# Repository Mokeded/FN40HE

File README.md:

# FN40HE

FN40HE is a 40%, Hall-effect mechanical keyboard PCB and firmware project. It
adapts the FN40 layout to magnetic (Hall-effect) switches, giving every key
analog actuation — per-key adjustable actuation points, Rapid Trigger,
SOCD/Null Bind, Dynamic Keystroke, and analog gamepad output — instead of a
fixed mechanical trip point.

## What's in this repository

- **KiCad hardware design** — `FN40HE.kicad_pro`/`.kicad_sch`/`.kicad_pcb`,
  a two-layer PCB with 57 independent Hall-sensor channels multiplexed down
  to an 8-channel ADC scan order, plus `FN40HE-plate.step` for the
  mechanical plate reference. `FN40_Project.pretty`, `lib`, `fp-lib-table`,
  and `sym-lib-table` are the local footprint/symbol libraries needed to
  open the project without external dependencies.
- **Firmware** (`firmware/`) — a [libhmk](https://github.com/libhmk/libhmk)-derived
  build configured for the `fn40he` board target, with prebuilt DFU
  artifacts in `firmware/build/` and full source under `firmware/source/`
  for rebuilding.
- **Manufacturing and assembly data** — `FN40HE-BOM.csv` (bill of
  materials for all assembly variants), `FN40HE-ASSEMBLY.md` (which
  mutually-exclusive switch/sensor positions to populate per variant),
  `FN40HE-sensor-map.csv` and `FN40HE-mux-map.csv` (physical-to-firmware
  key mapping), and `manufacturing/FN40HE-Gerbers-JLCPCB.zip` (bare-board
  fab archive).
- **Verification records** — `FN40HE-DRC.rpt` and `FN40HE-ERC.rpt` (PCB/
  schematic check reports) and `FN40HE-J1-WAIVER.md` (documented DRC
  waiver and inspection requirement for the J1 connector footprint).

See `FN40HE-README.md` for release status, build/flash instructions, and
firmware feature details.

## Assembly variants

The board supports three populate/DNP variants sharing one PCB:
**Universal57** (all 57 sensors populated — the released default),
**SplitSpace**, and **SevenUnit** (alternate bottom-row layouts). See
`FN40HE-ASSEMBLY.md` and the DNP columns in `FN40HE-BOM.csv` before
ordering assembly.

## License

This project incorporates GPLv3-derived hardware design and firmware work.
See `LICENSE`. Retain source, license, and attribution when redistributing
modifications.

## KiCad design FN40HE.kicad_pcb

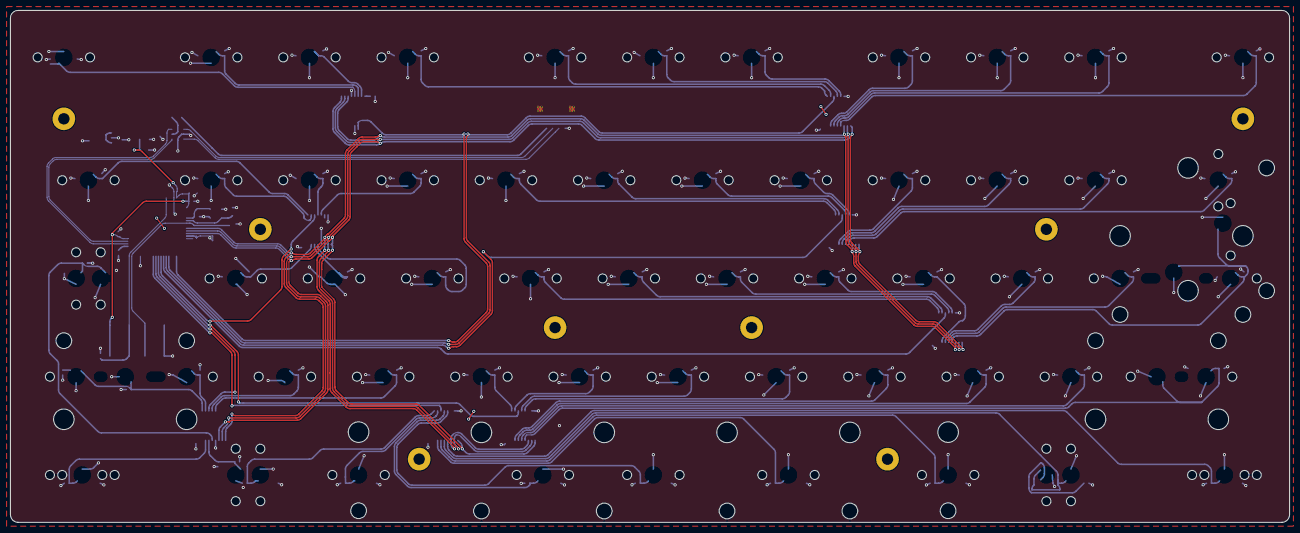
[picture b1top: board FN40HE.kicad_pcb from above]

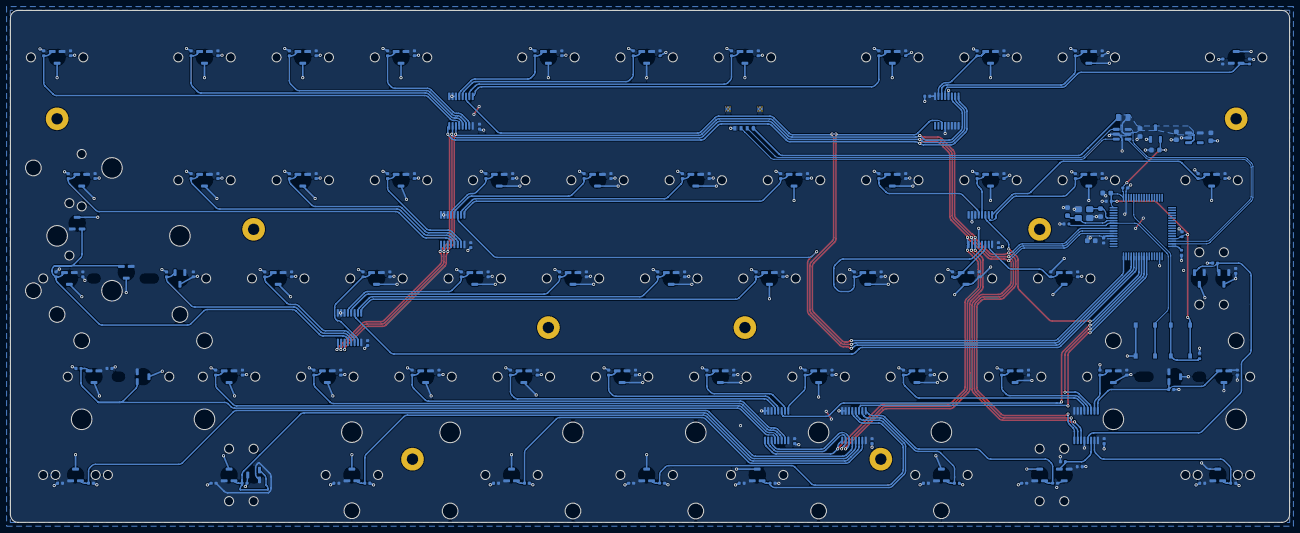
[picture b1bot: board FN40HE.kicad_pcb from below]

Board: 2 copper layers, 248.0 x 99.2 mm, 234 parts (219 on the bottom side), 82 nets.

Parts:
AM1: SN74LV4051A; AM1_TSSOP-16_4.4x5mm_P0.65mm
AM2: SN74LV4051A; AM2_TSSOP-16_4.4x5mm_P0.65mm
AM3: SN74LV4051A; AM3_TSSOP-16_4.4x5mm_P0.65mm
AM4: SN74LV4051A; AM4_TSSOP-16_4.4x5mm_P0.65mm
AM5: SN74LV4051A; AM5_TSSOP-16_4.4x5mm_P0.65mm
AM6: SN74LV4051A; AM6_TSSOP-16_4.4x5mm_P0.65mm
AM7: SN74LV4051A; AM7_TSSOP-16_4.4x5mm_P0.65mm
AM8: SN74LV4051A; AM8_TSSOP-16_4.4x5mm_P0.65mm
C1: 100n; C1_C_0402_1005Metric
C2: 4.7n; C2_C_0402_1005Metric
C3: 100n; C3_C_0402_1005Metric
C4: 4.7n; C4_C_0402_1005Metric
C5: 100n; C5_C_0402_1005Metric
C6: 4.7n; C6_C_0402_1005Metric
C7: 100n; C7_C_0402_1005Metric
C8: 4.7n; C8_C_0402_1005Metric
C9: 100n; C9_C_0402_1005Metric
C10: 4.7n; C10_C_0402_1005Metric
C11: 100n; C11_C_0402_1005Metric
C12: 4.7n; C12_C_0402_1005Metric
C13: 100n; C13_C_0402_1005Metric
C14: 4.7n; C14_C_0402_1005Metric
C15: 100n; C15_C_0402_1005Metric
C16: 4.7n; C16_C_0402_1005Metric
C17: 100n; C17_C_0402_1005Metric
C18: 4.7n; C18_C_0402_1005Metric
C19: 100n; C19_C_0402_1005Metric
C20: 4.7n; C20_C_0402_1005Metric
C21: 100n; C21_C_0402_1005Metric
C22: 4.7n; C22_C_0402_1005Metric
C23: 100n; C23_C_0402_1005Metric
C24: 4.7n; C24_C_0402_1005Metric
C25: 100n; C25_C_0402_1005Metric
C26: 4.7n; C26_C_0402_1005Metric
C27: 100n; C27_C_0402_1005Metric
C28: 4.7n; C28_C_0402_1005Metric
C29: 100n; C29_C_0402_1005Metric
C30: 4.7n; C30_C_0402_1005Metric
C31: 100n; C31_C_0402_1005Metric
C32: 4.7n; C32_C_0402_1005Metric
C33: 100n; C33_C_0402_1005Metric
C34: 4.7n; C34_C_0402_1005Metric
C35: 100n; C35_C_0402_1005Metric
C36: 4.7n; C36_C_0402_1005Metric
C37: 100n; C37_C_0402_1005Metric
C38: 4.7n; C38_C_0402_1005Metric
C39: 100n; C39_C_0402_1005Metric
C40: 4.7n; C40_C_0402_1005Metric
C41: 100n; C41_C_0402_1005Metric
C42: 4.7n; C42_C_0402_1005Metric
C43: 100n; C43_C_0402_1005Metric
C44: 4.7n; C44_C_0402_1005Metric
C45: 100n; C45_C_0402_1005Metric
C46: 4.7n; C46_C_0402_1005Metric
C47: 100n; C47_C_0402_1005Metric
C48: 4.7n; C48_C_0402_1005Metric
C49: 100n; C49_C_0402_1005Metric
C50: 4.7n; C50_C_0402_1005Metric
C51: 100n; C51_C_0402_1005Metric
C52: 4.7n; C52_C_0402_1005Metric
C53: 100n; C53_C_0402_1005Metric
C54: 4.7n; C54_C_0402_1005Metric
C55: 100n; C55_C_0402_1005Metric
C56: 4.7n; C56_C_0402_1005Metric
C57: 100n; C57_C_0402_1005Metric
C58: 4.7n; C58_C_0402_1005Metric
C59: 100n; C59_C_0402_1005Metric
C60: 4.7n; C60_C_0402_1005Metric
C61: 100n; C61_C_0402_1005Metric
C62: 4.7n; C62_C_0402_1005Metric
C63: 100n; C63_C_0402_1005Metric
C64: 4.7n; C64_C_0402_1005Metric
C65: 100n; C65_C_0402_1005Metric
C66: 4.7n; C66_C_0402_1005Metric
C67: 100n; C67_C_0402_1005Metric
C68: 4.7n; C68_C_0402_1005Metric
C69: 100n; C69_C_0402_1005Metric
C70: 4.7n; C70_C_0402_1005Metric
C71: 100n; C71_C_0402_1005Metric
C72: 4.7n; C72_C_0402_1005Metric
C73: 100n; C73_C_0402_1005Metric
C74: 4.7n; C74_C_0402_1005Metric
C75: 100n; C75_C_0402_1005Metric
C76: 4.7n; C76_C_0402_1005Metric
C77: 100n; C77_C_0402_1005Metric
C78: 4.7n; C78_C_0402_1005Metric
C79: 100n; C79_C_0402_1005Metric
C80: 4.7n; C80_C_0402_1005Metric
C81: 100n; C81_C_0402_1005Metric
C82: 4.7n; C82_C_0402_1005Metric
C83: 100n; C83_C_0402_1005Metric
C84: 4.7n; C84_C_0402_1005Metric
C85: 100n; C85_C_0402_1005Metric
C86: 4.7n; C86_C_0402_1005Metric
C87: 100n; C87_C_0402_1005Metric
C88: 4.7n; C88_C_0402_1005Metric
C89: 100n; C89_C_0402_1005Metric
C90: 4.7n; C90_C_0402_1005Metric
C91: 100n; C91_C_0402_1005Metric
C92: 4.7n; C92_C_0402_1005Metric
C93: 100n; C93_C_0402_1005Metric
C94: 4.7n; C94_C_0402_1005Metric
C95: 100n; C95_C_0402_1005Metric
C96: 4.7n; C96_C_0402_1005Metric
C97: 100n; C97_C_0402_1005Metric
C98: 4.7n; C98_C_0402_1005Metric
C99: 100n; C99_C_0402_1005Metric
C100: 4.7n; C100_C_0402_1005Metric
C101: 100n; C101_C_0402_1005Metric
C102: 4.7n; C102_C_0402_1005Metric
C103: 100n; C103_C_0402_1005Metric
C104: 4.7n; C104_C_0402_1005Metric
C105: 100n; C105_C_0402_1005Metric
C106: 4.7n; C106_C_0402_1005Metric
C107: 100n; C107_C_0402_1005Metric
C108: 4.7n; C108_C_0402_1005Metric
C109: 100n; C109_C_0402_1005Metric
C110: 4.7n; C110_C_0402_1005Metric
C111: 100n; C111_C_0402_1005Metric
C112: 4.7n; C112_C_0402_1005Metric
C113: 100n; C113_C_0402_1005Metric
C114: 4.7n; C114_C_0402_1005Metric
C139: 100n; C139_C_0402_1005Metric
C140: 100n; C140_C_0402_1005Metric
C141: 100n; C141_C_0402_1005Metric
C142: 100n; C142_C_0402_1005Metric
C143: 100n; C143_C_0402_1005Metric
C144: 100n; C144_C_0402_1005Metric
C145: 100n; C145_C_0402_1005Metric
C146: 100n; C146_C_0402_1005Metric
C148: 2.2u; C148_C_0603_1608Metric
C149: 2.2u; C149_C_0603_1608Metric
C150: 2.2u; C150_C_0603_1608Metric
C151: 2.2u; C151_C_0603_1608Metric
C152: 30p; C152_C_0603_1608Metric
C153: 30p; C153_C_0603_1608Metric
C154: 100n; C154_C_0402_1005Metric
C155: 100n; C155_C_0402_1005Metric
C156: 100n; C156_C_0402_1005Metric
C157: 10u; C157_C_0603_1608Metric
C158: 100n; C158_C_0402_1005Metric
C159: 1u; C159_C_0603_1608Metric
C160: 100n; C160_C_0402_1005Metric
F1: BSMD0805-050-24V; F1_Fuse_0805_2012Metric
HE1: MT9102ET; HE1_MT9102ET_Key_1.00u
HE2: MT9102ET; HE2_MT9102ET_Key_1.00u
HE3: MT9102ET; HE3_MT9102ET_Key_1.00u
HE4: MT9102ET; HE4_MT9102ET_Key_1.00u
HE5: MT9102ET; HE5_MT9102ET_Key_1.00u
HE6: MT9102ET; HE6_MT9102ET_Key_1.00u
HE7: MT9102ET; HE7_MT9102ET_Key_1.00u
HE8: MT9102ET; HE8_MT9102ET_Key_1.00u
HE9: MT9102ET; HE9_MT9102ET_Key_1.00u
HE10: MT9102ET; HE10_MT9102ET_Key_1.00u
HE11: MT9102ET; HE11_MT9102ET_Key_1.00u
HE12: MT9102ET; HE12_MT9102ET_Key_1.50u
HE13: MT9102ET; HE13_MT9102ET_Key_1.00u
HE14: MT9102ET; HE14_MT9102ET_Key_1.00u
HE15: MT9102ET; HE15_MT9102ET_Key_1.00u
HE16: MT9102ET; HE16_MT9102ET_Key_1.00u
HE17: MT9102ET; HE17_MT9102ET_Key_1.00u
HE18: MT9102ET; HE18_MT9102ET_Key_1.00u
HE19: MT9102ET; HE19_MT9102ET_Key_1.00u
HE20: MT9102ET; HE20_MT9102ET_Key_1.00u
HE21: MT9102ET; HE21_MT9102ET_Key_1.00u
HE22: MT9102ET; HE22_MT9102ET_Key_1.00u
HE23: MT9102ET; HE23_MT9102ET_Key_1.50u
HE24: MT9102ET; HE24_MT9102ET_Key_1.75u_90deg
HE24A: MT9102ET_ALT_SW24_1_DNP; HE24A_MT9102ET_KLE_SW24_1
HE25: MT9102ET; HE25_MT9102ET_Key_1.00u
HE26: MT9102ET; HE26_MT9102ET_Key_1.00u
HE27: MT9102ET; HE27_MT9102ET_Key_1.00u
HE28: MT9102ET; HE28_MT9102ET_Key_1.00u
HE29: MT9102ET; HE29_MT9102ET_Key_1.00u
HE30: MT9102ET; HE30_MT9102ET_Key_1.00u
HE31: MT9102ET; HE31_MT9102ET_Key_1.00u
HE32: MT9102ET; HE32_MT9102ET_Key_1.00u
HE33: MT9102ET; HE33_MT9102ET_Key_1.00u
HE34: MT9102ET; HE34_MT9102ET_Key_1.00u
HE35: MT9102ET; HE35_MT9102ET_Key_1.25u
HE35A: MT9102ET_ALT_SW35_1_DNP; HE35A_MT9102ET_KLE_SW35_1
HE35B: MT9102ET_ALT_SW35_2_DNP; HE35B_MT9102ET_KLE_SW35_2
HE36: MT9102ET; HE36_MT9102ET_Key_1.25u
HE36A: MT9102ET_ALT_SW36_1_DNP; HE36A_MT9102ET_KLE_SW36_1
HE37: MT9102ET; HE37_MT9102ET_Key_1.00u
HE38: MT9102ET; HE38_MT9102ET_Key_1.00u
HE39: MT9102ET; HE39_MT9102ET_Key_1.00u
HE40: MT9102ET; HE40_MT9102ET_Key_1.00u
HE41: MT9102ET; HE41_MT9102ET_Key_1.00u
HE42: MT9102ET; HE42_MT9102ET_Key_1.00u
HE43: MT9102ET; HE43_MT9102ET_Key_1.00u
HE44: MT9102ET; HE44_MT9102ET_Key_1.00u
HE45: MT9102ET; HE45_MT9102ET_Key_1.00u
HE46: MT9102ET; HE46_MT9102ET_Key_1.00u
HE47: MT9102ET; HE47_MT9102ET_Key_1.75u
HE47A: MT9102ET_ALT_SW47_1_DNP; HE47A_MT9102ET_KLE_SW47_1
HE48: MT9102ET; HE48_MT9102ET_Key_1.50u
HE48A: MECHANICAL_ALT_SHARED_SENSOR_DNP; HE48A_MECHANICAL_ALT
HE49: MT9102ET; HE49_MT9102ET_Key_1.00u
HE50: MT9102ET; HE50_MT9102ET_Key_2.75u
HE51: MT9102ET; HE51_MT9102ET_Key_2.25u
HE52: MT9102ET; HE52_MT9102ET_Key_1.00u
HE53: MT9102ET; HE53_MT9102ET_Key_1.50u
HE53A: MECHANICAL_ALT_SHARED_SENSOR_DNP; HE53A_MECHANICAL_ALT
HE54: MT9102ET; HE54_MT9102ET_Key_1.50u
HE55: MT9102ET; HE55_MT9102ET_Key_1.00u
HE56: MT9102ET; HE56_MT9102ET_Key_7.00u
HE57: MT9102ET; HE57_MT9102ET_Key_1.50u
HE57A: MT9102ET_ALT_SW56_1_DNP; HE57A_MT9102ET_KLE_SW56_1
J1: Unified_Daughterboard_4P; J1_MOLEX_781710004_MountingReliefs
MH1, MH2, MH3, MH4, MH5, MH6, MH7, MH8: M2_PLATE_STANDOFF; MountingHole_2.2mm_M2_Pad
R3: 12k; R3_R_0402_1005Metric
R4: 12k; R4_R_0402_1005Metric
S1: FN40_PCB_STABILIZER_HOLES; S1_STABILIZER_HOLES
S2: FN40_PCB_STABILIZER_HOLES; S2_STABILIZER_HOLES
S3: FN40_PCB_STABILIZER_HOLES; S3_STABILIZER_HOLES
S4: FN40_PCB_STABILIZER_HOLES; S4_STABILIZER_HOLES
S5: FN40_PCB_STABILIZER_HOLES; S5_STABILIZER_HOLES
S6: FN40_PCB_STABILIZER_HOLES; S6_STABILIZER_HOLES
S7: FN40_PCB_STABILIZER_HOLES; S7_STABILIZER_HOLES
SW1: TS-1187A-B-A-B; SW1_SW_Push_1P1T_XKB_TS-1187A
SW2: TS-1187A-B-A-B; SW2_SW_Push_1P1T_XKB_TS-1187A
U1: USBLC6-2SC6; U1_SOT-23-6
U2: TLV75733PDBV; U2_SOT-23-5
U3: XC6206P332MR-G; U3_SOT-23-3
U4: AT32F405RCT7; U4_LQFP-64_10x10mm_P0.5mm
Y1: X322512MSB4SI; Y1_Crystal_SMD_3225-4Pin_3.2x2.5mm

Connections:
+3.3V: C151.1, C154.1, C155.1, C156.1, C157.1, SW2.2, U3.2 (VO), U4.1 (VDD), U4.36 (VDD), U4.64 (VDD)
+3.3VA: AM1.16 (VDD), AM2.16 (VDD), AM3.16 (VDD), AM4.16 (VDD), AM5.16 (VDD), AM6.16 (VDD), AM7.16 (VDD), AM8.16 (VDD), C1.1, C3.1, C5.1, C7.1, C9.1, C11.1, C13.1, C15.1, C17.1, C19.1, C21.1, C23.1, C25.1, C27.1, C29.1, C31.1, C33.1, C35.1, C37.1, C39.1, C41.1, C43.1, C45.1, C47.1, C49.1, C51.1, C53.1, C55.1, C57.1, C59.1, C61.1, C63.1, C65.1, C67.1, C69.1, C71.1, C73.1, C75.1, C77.1, C79.1, C81.1, C83.1, C85.1, C87.1, C89.1, C91.1, C93.1, C95.1, C97.1, C99.1, C101.1, C103.1, C105.1, C107.1, C109.1, C111.1, C113.1, C139.1, C140.1, C141.1, C142.1, C143.1, C144.1, C145.1, C146.1, C149.1, C158.1, C159.1, HE1.1 (VCC), HE2.1 (VCC), HE3.1 (VCC), HE4.1 (VCC), HE5.1 (VCC), HE6.1 (VCC), HE7.1 (VCC), HE8.1 (VCC), HE9.1 (VCC), HE10.1 (VCC), HE11.1 (VCC), HE12.1 (VCC), HE13.1 (VCC), HE14.1 (VCC), HE15.1 (VCC), HE16.1 (VCC), HE17.1 (VCC), HE18.1 (VCC), HE19.1 (VCC), HE20.1 (VCC), HE21.1 (VCC), HE22.1 (VCC), HE23.1 (VCC), HE24.1 (VCC), HE24A.1 (VCC), HE25.1 (VCC), HE26.1 (VCC), HE27.1 (VCC), HE28.1 (VCC), HE29.1 (VCC), HE30.1 (VCC), HE31.1 (VCC), HE32.1 (VCC), HE33.1 (VCC), HE34.1 (VCC), HE35.1 (VCC), HE35A.1 (VCC), HE35B.1 (VCC), HE36.1 (VCC), HE36A.1 (VCC), HE37.1 (VCC), HE38.1 (VCC), HE39.1 (VCC), HE40.1 (VCC), HE41.1 (VCC), HE42.1 (VCC), HE43.1 (VCC), HE44.1 (VCC), HE45.1 (VCC), HE46.1 (VCC), HE47.1 (VCC), HE47A.1 (VCC), HE48.1 (VCC), HE49.1 (VCC), HE50.1 (VCC), HE51.1 (VCC), HE52.1 (VCC), HE53.1 (VCC), HE54.1 (VCC), HE55.1 (VCC), HE56.1 (VCC), HE57.1 (VCC), HE57A.1 (VCC), U2.5 (OUT), U4.13 (VDDA)
+5V: C148.1, C150.1, F1.2, U1.5 (VBUS), U2.1 (IN), U2.3 (EN), U3.3 (VI)
BOOT0: R4.1, SW2.1, U4.60 (PF11/BOOT0)
GND: AM1.4 (X7), AM1.5 (X5), AM1.6 (Inh), AM1.7 (VEE), AM1.8 (VSS), AM1.12 (X3), AM2.6 (Inh), AM2.7 (VEE), AM2.8 (VSS), AM3.6 (Inh), AM3.7 (VEE), AM3.8 (VSS), AM4.6 (Inh), AM4.7 (VEE), AM4.8 (VSS), AM5.6 (Inh), AM5.7 (VEE), AM5.8 (VSS), AM5.12 (X3), AM6.6 (Inh), AM6.7 (VEE), AM6.8 (VSS), AM7.6 (Inh), AM7.7 (VEE), AM7.8 (VSS), AM7.12 (X3), AM8.6 (Inh), AM8.7 (VEE), AM8.8 (VSS), C1.2, C2.2, C3.2, C4.2, C5.2, C6.2, C7.2, C8.2, C9.2, C10.2, C11.2, C12.2, C13.2, C14.2, C15.2, C16.2, C17.2, C18.2, C19.2, C20.2, C21.2, C22.2, C23.2, C24.2, C25.2, C26.2, C27.2, C28.2, C29.2, C30.2, C31.2, C32.2, C33.2, C34.2, C35.2, C36.2, C37.2, C38.2, C39.2, C40.2, C41.2, C42.2, C43.2, C44.2, C45.2, C46.2, C47.2, C48.2, C49.2, C50.2, C51.2, C52.2, C53.2, C54.2, C55.2, C56.2, C57.2, C58.2, C59.2, C60.2, C61.2, C62.2, C63.2, C64.2, C65.2, C66.2, C67.2, C68.2, C69.2, C70.2, C71.2, C72.2, C73.2, C74.2, C75.2, C76.2, C77.2, C78.2, C79.2, C80.2, C81.2, C82.2, C83.2, C84.2, C85.2, C86.2, C87.2, C88.2, C89.2, C90.2, C91.2, C92.2, C93.2, C94.2, C95.2, C96.2, C97.2, C98.2, C99.2, C100.2, C101.2, C102.2, C103.2, C104.2, C105.2, C106.2, C107.2, C108.2, C109.2, C110.2, C111.2, C112.2, C113.2, C114.2, C139.2, C140.2, C141.2, C142.2, C143.2, C144.2, C145.2, C146.2, C148.2, C149.2, C150.2, C151.2, C152.2, C153.2, C154.2, C155.2, C156.2, C157.2, C158.2, C159.2, C160.2, HE1.3 (GND), HE2.3 (GND), HE3.3 (GND), HE4.3 (GND), HE5.3 (GND), HE6.3 (GND), HE7.3 (GND), HE8.3 (GND), HE9.3 (GND), HE10.3 (GND), HE11.3 (GND), HE12.3 (GND), HE13.3 (GND), HE14.3 (GND), HE15.3 (GND), HE16.3 (GND), HE17.3 (GND), HE18.3 (GND), HE19.3 (GND), HE20.3 (GND), HE21.3 (GND), HE22.3 (GND), HE23.3 (GND), HE24.3 (GND), HE24A.3 (GND), HE25.3 (GND), HE26.3 (GND), HE27.3 (GND), HE28.3 (GND), HE29.3 (GND), HE30.3 (GND), HE31.3 (GND), HE32.3 (GND), HE33.3 (GND), HE34.3 (GND), HE35.3 (GND), HE35A.3 (GND), HE35B.3 (GND), HE36.3 (GND), HE36A.3 (GND), HE37.3 (GND), HE38.3 (GND), HE39.3 (GND), HE40.3 (GND), HE41.3 (GND), HE42.3 (GND), HE43.3 (GND), HE44.3 (GND), HE45.3 (GND), HE46.3 (GND), HE47.3 (GND), HE47A.3 (GND), HE48.3 (GND), HE49.3 (GND), HE50.3 (GND), HE51.3 (GND), HE52.3 (GND), HE53.3 (GND), HE54.3 (GND), HE55.3 (GND), HE56.3 (GND), HE57.3 (GND), HE57A.3 (GND), J1.4, J1.MP (MountPin), R3.1, R4.2, SW1.2, U1.2 (GND), U2.2 (GND), U3.1 (GND), U4.12 (VSSA), U4.31 (VSS), U4.63 (VSS), Y1.2, Y1.4
HE1: AM1.13 (X0), C2.1, HE1.2 (OUT)
HE2: AM1.14 (X1), C4.1, HE2.2 (OUT)
HE3: AM1.15 (X2), C6.1, HE3.2 (OUT)
HE4: AM2.1 (X4), C8.1, HE4.2 (OUT)
HE5: AM2.2 (X6), C10.1, HE5.2 (OUT)
HE6: AM2.4 (X7), C12.1, HE6.2 (OUT)
HE7: AM2.5 (X5), C14.1, HE7.2 (OUT)
HE8: AM2.15 (X2), C16.1, HE8.2 (OUT)
HE9: AM2.14 (X1), C18.1, HE9.2 (OUT)
HE10: AM2.13 (X0), C20.1, HE10.2 (OUT)
HE11: AM2.12 (X3), C22.1, HE11.2 (OUT)
HE12: AM5.1 (X4), C24.1, HE12.2 (OUT)
HE13: AM5.2 (X6), C26.1, HE13.2 (OUT)
HE14: AM5.4 (X7), C28.1, HE14.2 (OUT)
HE15: AM5.5 (X5), C30.1, HE15.2 (OUT)
HE16: AM3.1 (X4), C32.1, HE16.2 (OUT)
HE17: AM3.2 (X6), C34.1, HE17.2 (OUT)
HE18: AM3.4 (X7), C36.1, HE18.2 (OUT)
HE19: AM3.5 (X5), C38.1, HE19.2 (OUT)
HE20: AM3.15 (X2), C40.1, HE20.2 (OUT)
HE21: AM3.14 (X1), C42.1, HE21.2 (OUT)
HE22: AM3.13 (X0), C44.1, HE22.2 (OUT)
HE23: AM3.12 (X3), C46.1, HE23.2 (OUT)
HE24: AM7.13 (X0), C48.1, HE24.2 (OUT), HE24A.2 (OUT)
HE25: AM5.15 (X2), C50.1, HE25.2 (OUT)
HE26: AM5.14 (X1), C52.1, HE26.2 (OUT)
HE27: AM5.13 (X0), C54.1, HE27.2 (OUT)
HE28: AM4.1 (X4), C56.1, HE28.2 (OUT)
HE29: AM4.2 (X6), C58.1, HE29.2 (OUT)
HE30: AM4.4 (X7), C60.1, HE30.2 (OUT)
HE31: AM4.5 (X5), C62.1, HE31.2 (OUT)
HE32: AM4.15 (X2), C64.1, HE32.2 (OUT)
HE33: AM4.14 (X1), C66.1, HE33.2 (OUT)
HE34: AM4.13 (X0), C68.1, HE34.2 (OUT)
HE35: AM4.12 (X3), C70.1, HE35.2 (OUT), HE35A.2 (OUT), HE35B.2 (OUT)
HE36: AM7.1 (X4), C72.1, HE36.2 (OUT), HE36A.2 (OUT)
HE37: AM7.2 (X6), C74.1, HE37.2 (OUT)
HE38: AM7.4 (X7), C76.1, HE38.2 (OUT)
HE39: AM7.5 (X5), C78.1, HE39.2 (OUT)
HE40: AM6.1 (X4), C80.1, HE40.2 (OUT)
HE41: AM6.2 (X6), C82.1, HE41.2 (OUT)
HE42: AM6.4 (X7), C84.1, HE42.2 (OUT)
HE43: AM6.5 (X5), C86.1, HE43.2 (OUT)
HE44: AM6.15 (X2), C88.1, HE44.2 (OUT)
HE45: AM6.14 (X1), C90.1, HE45.2 (OUT)
HE46: AM6.13 (X0), C92.1, HE46.2 (OUT)
HE47: AM6.12 (X3), C94.1, HE47.2 (OUT), HE47A.2 (OUT)
HE48: AM7.15 (X2), C96.1, HE48.2 (OUT)
HE49: AM8.2 (X6), C98.1, HE49.2 (OUT)
HE50: AM8.4 (X7), C100.1, HE50.2 (OUT)
HE51: AM8.15 (X2), C102.1, HE51.2 (OUT)
HE52: AM8.14 (X1), C104.1, HE52.2 (OUT)
HE53: AM8.12 (X3), C106.1, HE53.2 (OUT)
HE54: AM7.14 (X1), C108.1, HE54.2 (OUT)
HE55: AM8.1 (X4), C110.1, HE55.2 (OUT)
HE56: AM8.5 (X5), C112.1, HE56.2 (OUT)
HE57: AM8.13 (X0), C114.1, HE57.2 (OUT), HE57A.2 (OUT)
HEXT_IN: C152.1, U4.5 (PF0/HEXT_IN), Y1.1
HEXT_OUT: C153.1, U4.6 (PF1/HEXT_OUT), Y1.3
MUX_OUT_1: AM1.3 (X), U4.17 (PA3)
MUX_OUT_2: AM2.3 (X), U4.20 (PA4)
MUX_OUT_3: AM3.3 (X), U4.21 (PA5)
MUX_OUT_4: AM4.3 (X), U4.22 (PA6)
MUX_OUT_5: AM5.3 (X), U4.23 (PA7)
MUX_OUT_6: AM6.3 (X), U4.24 (PC4)
MUX_OUT_7: AM7.3 (X), U4.25 (PC5)
MUX_OUT_8: AM8.3 (X), U4.26 (PB0)
MUX_SELECT_0: AM1.11 (A), AM2.11 (A), AM3.11 (A), AM4.11 (A), AM5.11 (A), AM6.11 (A), AM7.9 (C), AM8.11 (A), U4.9 (PC1)
MUX_SELECT_1: AM1.10 (B), AM2.10 (B), AM3.10 (B), AM4.10 (B), AM5.10 (B), AM6.10 (B), AM7.10 (B), AM8.10 (B), U4.10 (PC2)
MUX_SELECT_2: AM1.9 (C), AM2.9 (C), AM3.9 (C), AM4.9 (C), AM5.9 (C), AM6.9 (C), AM7.11 (A), AM8.9 (C), U4.11 (PC3)
NRST: C160.1, SW1.1, U4.7 (NRST)
unnamed: R3.2, U4.33 (OTGHS1_R)
USB_D+: U1.4 (I/O2), U4.35 (OTGHS1_D+)
USB_D-: U1.6 (I/O1), U4.34 (OTGHS1_D-)
USB_PLUG_D+: J1.3, U1.3 (I/O2)
USB_PLUG_D-: J1.2, U1.1 (I/O1)
VBUS: F1.1, J1.1

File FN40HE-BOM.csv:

Item,Value,Package,Manufacturer,Manufacturer_Part_Number,Qty_Universal57,Qty_SplitSpace,DNP_SplitSpace,Qty_SevenUnit,DNP_SevenUnit,References_Universal57,Notes
1,SN74LV4051A,TSSOP-16_4.4x5mm_P0.65mm,Texas Instruments,SN74LV4051APWR,8,8,,8,,AM1 AM2 AM3 AM4 AM5 AM6 AM7 AM8,"8:1 analog mux, TSSOP-16"
2,100n,C_0402_1005Metric,TORCH,CC0402X7R16V104KN,70,68,C109 C111,65,C97 C99 C101 C103 C107,C1 C3 C5 C7 C9 C11 C13 C15 C17 C19 C21 C23 C25 C27 C29 C31 C33 C35 C37 C39 C41 C43 C45 C47 C49 C51 C53 C55 C57 C59 C61 C63 C65 C67 C69 C71 C73 C75 C77 C79 C81 C83 C85 C87 C89 C91 C93 C95 C97 C99 C101 C103 C105 C107 C109 C111 C113 C139 C140 C141 C142 C143 C144 C145 C146 C154 C155 C156 C158 C160,"JLC/LCSC C53084507; X7R, 16 V, 10%; package C_0402_1005Metric; reconfirm stock before order"
3,4.7n,C_0402_1005Metric,Murata,GRM1555C1H472JE01D,57,55,C110 C112,52,C98 C100 C102 C104 C108,C2 C4 C6 C8 C10 C12 C14 C16 C18 C20 C22 C24 C26 C28 C30 C32 C34 C36 C38 C40 C42 C44 C46 C48 C50 C52 C54 C56 C58 C60 C62 C64 C66 C68 C70 C72 C74 C76 C78 C80 C82 C84 C86 C88 C90 C92 C94 C96 C98 C100 C102 C104 C106 C108 C110 C112 C114,"JLC/LCSC C1518204; C0G, 50 V, 5%; package C_0402_1005Metric; reconfirm stock before order"
4,2.2u,C_0603_1608Metric,Samsung Electro-Mechanics,CL10B225KP8NFNC,4,4,,4,,C148 C149 C150 C151,"JLC/LCSC C3905270; X7R, 10 V, 10%; package C_0603_1608Metric; reconfirm stock before order"
5,30p,C_0603_1608Metric,Samsung Electro-Mechanics,CL10C300JB8NNNC,2,2,,2,,C152 C153,"JLC/LCSC C22397; C0G, 50 V, 5%; package C_0603_1608Metric; reconfirm stock before order"
6,10u,C_0603_1608Metric,Yageo,CC0603MRX5R5BB106,1,1,,1,,C157,"JLC/LCSC C109454; X5R, 6.3 V, 20%; package C_0603_1608Metric; reconfirm stock before order"
7,1u,C_0603_1608Metric,Murata,GRM188R71A105KA61D,1,1,,1,,C159,"JLC/LCSC C97888; X7R, 10 V, 10%; package C_0603_1608Metric; reconfirm stock before order"
8,BSMD0805-050-24V,Fuse_0805_2012Metric,Approved equivalent,BSMD0805-050-24V,1,1,,1,,F1,"JLC/LCSC C910822; 0.5 A resettable fuse, 0805; reconfirm stock before order"
9,MT9102ET,MT9102ET / key-center footprint,NOVOSENSE / MagnTek,MT9102ET,57,55,HE55 HE56,52,HE49 HE50 HE51 HE52 HE54,HE1 HE2 HE3 HE4 HE5 HE6 HE7 HE8 HE9 HE10 HE11 HE12 HE13 HE14 HE15 HE16 HE17 HE18 HE19 HE20 HE21 HE22 HE23 HE24 HE25 HE26 HE27 HE28 HE29 HE30 HE31 HE32 HE33 HE34 HE35 HE36 HE37 HE38 HE39 HE40 HE41 HE42 HE43 HE44 HE45 HE46 HE47 HE48 HE49 HE50 HE51 HE52 HE53 HE54 HE55 HE56 HE57,Linear Hall-effect sensor; JLC/LCSC C5447698; verify polarity and switch magnet
10,Unified_Daughterboard_4P,MOLEX_781710004_MountingReliefs,Molex,781710004,1,1,,1,,J1,"JLC/LCSC C588524; Pico-EZmate 1.20 mm, 4 circuits; confirm mating cable and footprint drawing"
11,12k,R_0402_1005Metric,Yageo,RC0402FR-0712KL,2,2,,2,,R3 R4,"JLC/LCSC C114760; 1%, 1/16 W; package R_0402_1005Metric; reconfirm stock before order"
12,TS-1187A-B-A-B,SW_Push_1P1T_XKB_TS-1187A,XKB Industrial Precision,TS-1187A-B-A-B,2,2,,2,,SW1 SW2,"JLC/LCSC C318884; momentary tact switch; reconfirm stock before order"
13,USBLC6-2SC6,SOT-23-6,STMicroelectronics,USBLC6-2SC6,1,1,,1,,U1,"JLC/LCSC C7519; USB ESD protection; do not substitute a different manufacturer without review"
14,TLV75733PDBV,SOT-23-5,Texas Instruments,TLV75733PDBVR,1,1,,1,,U2,"JLC/LCSC C485517; 3.3 V LDO, SOT-23-5; reconfirm stock before order"
15,XC6206P332MR-G,SOT-23-3,Torex Semiconductor,XC6206P332MR-G,1,1,,1,,U3,"JLC/LCSC C5446; 3.3 V analog LDO, SOT-23-3; reconfirm stock before order"
16,AT32F405RCT7,LQFP-64_10x10mm_P0.5mm,Artery Technology,AT32F405RCT7,1,1,,1,,U4,"JLC/LCSC C47090415; 216 MHz MCU, LQFP-64; reconfirm stock before order"
17,X322512MSB4SI,Crystal_SMD_3225-4Pin_3.2x2.5mm,Yangxing Tech,X322512MSB4SI,1,1,,1,,Y1,"JLC/LCSC C9002; 12 MHz, 20 pF crystal, 3.2 x 2.5 mm, 4 pad; reconfirm stock before order"
